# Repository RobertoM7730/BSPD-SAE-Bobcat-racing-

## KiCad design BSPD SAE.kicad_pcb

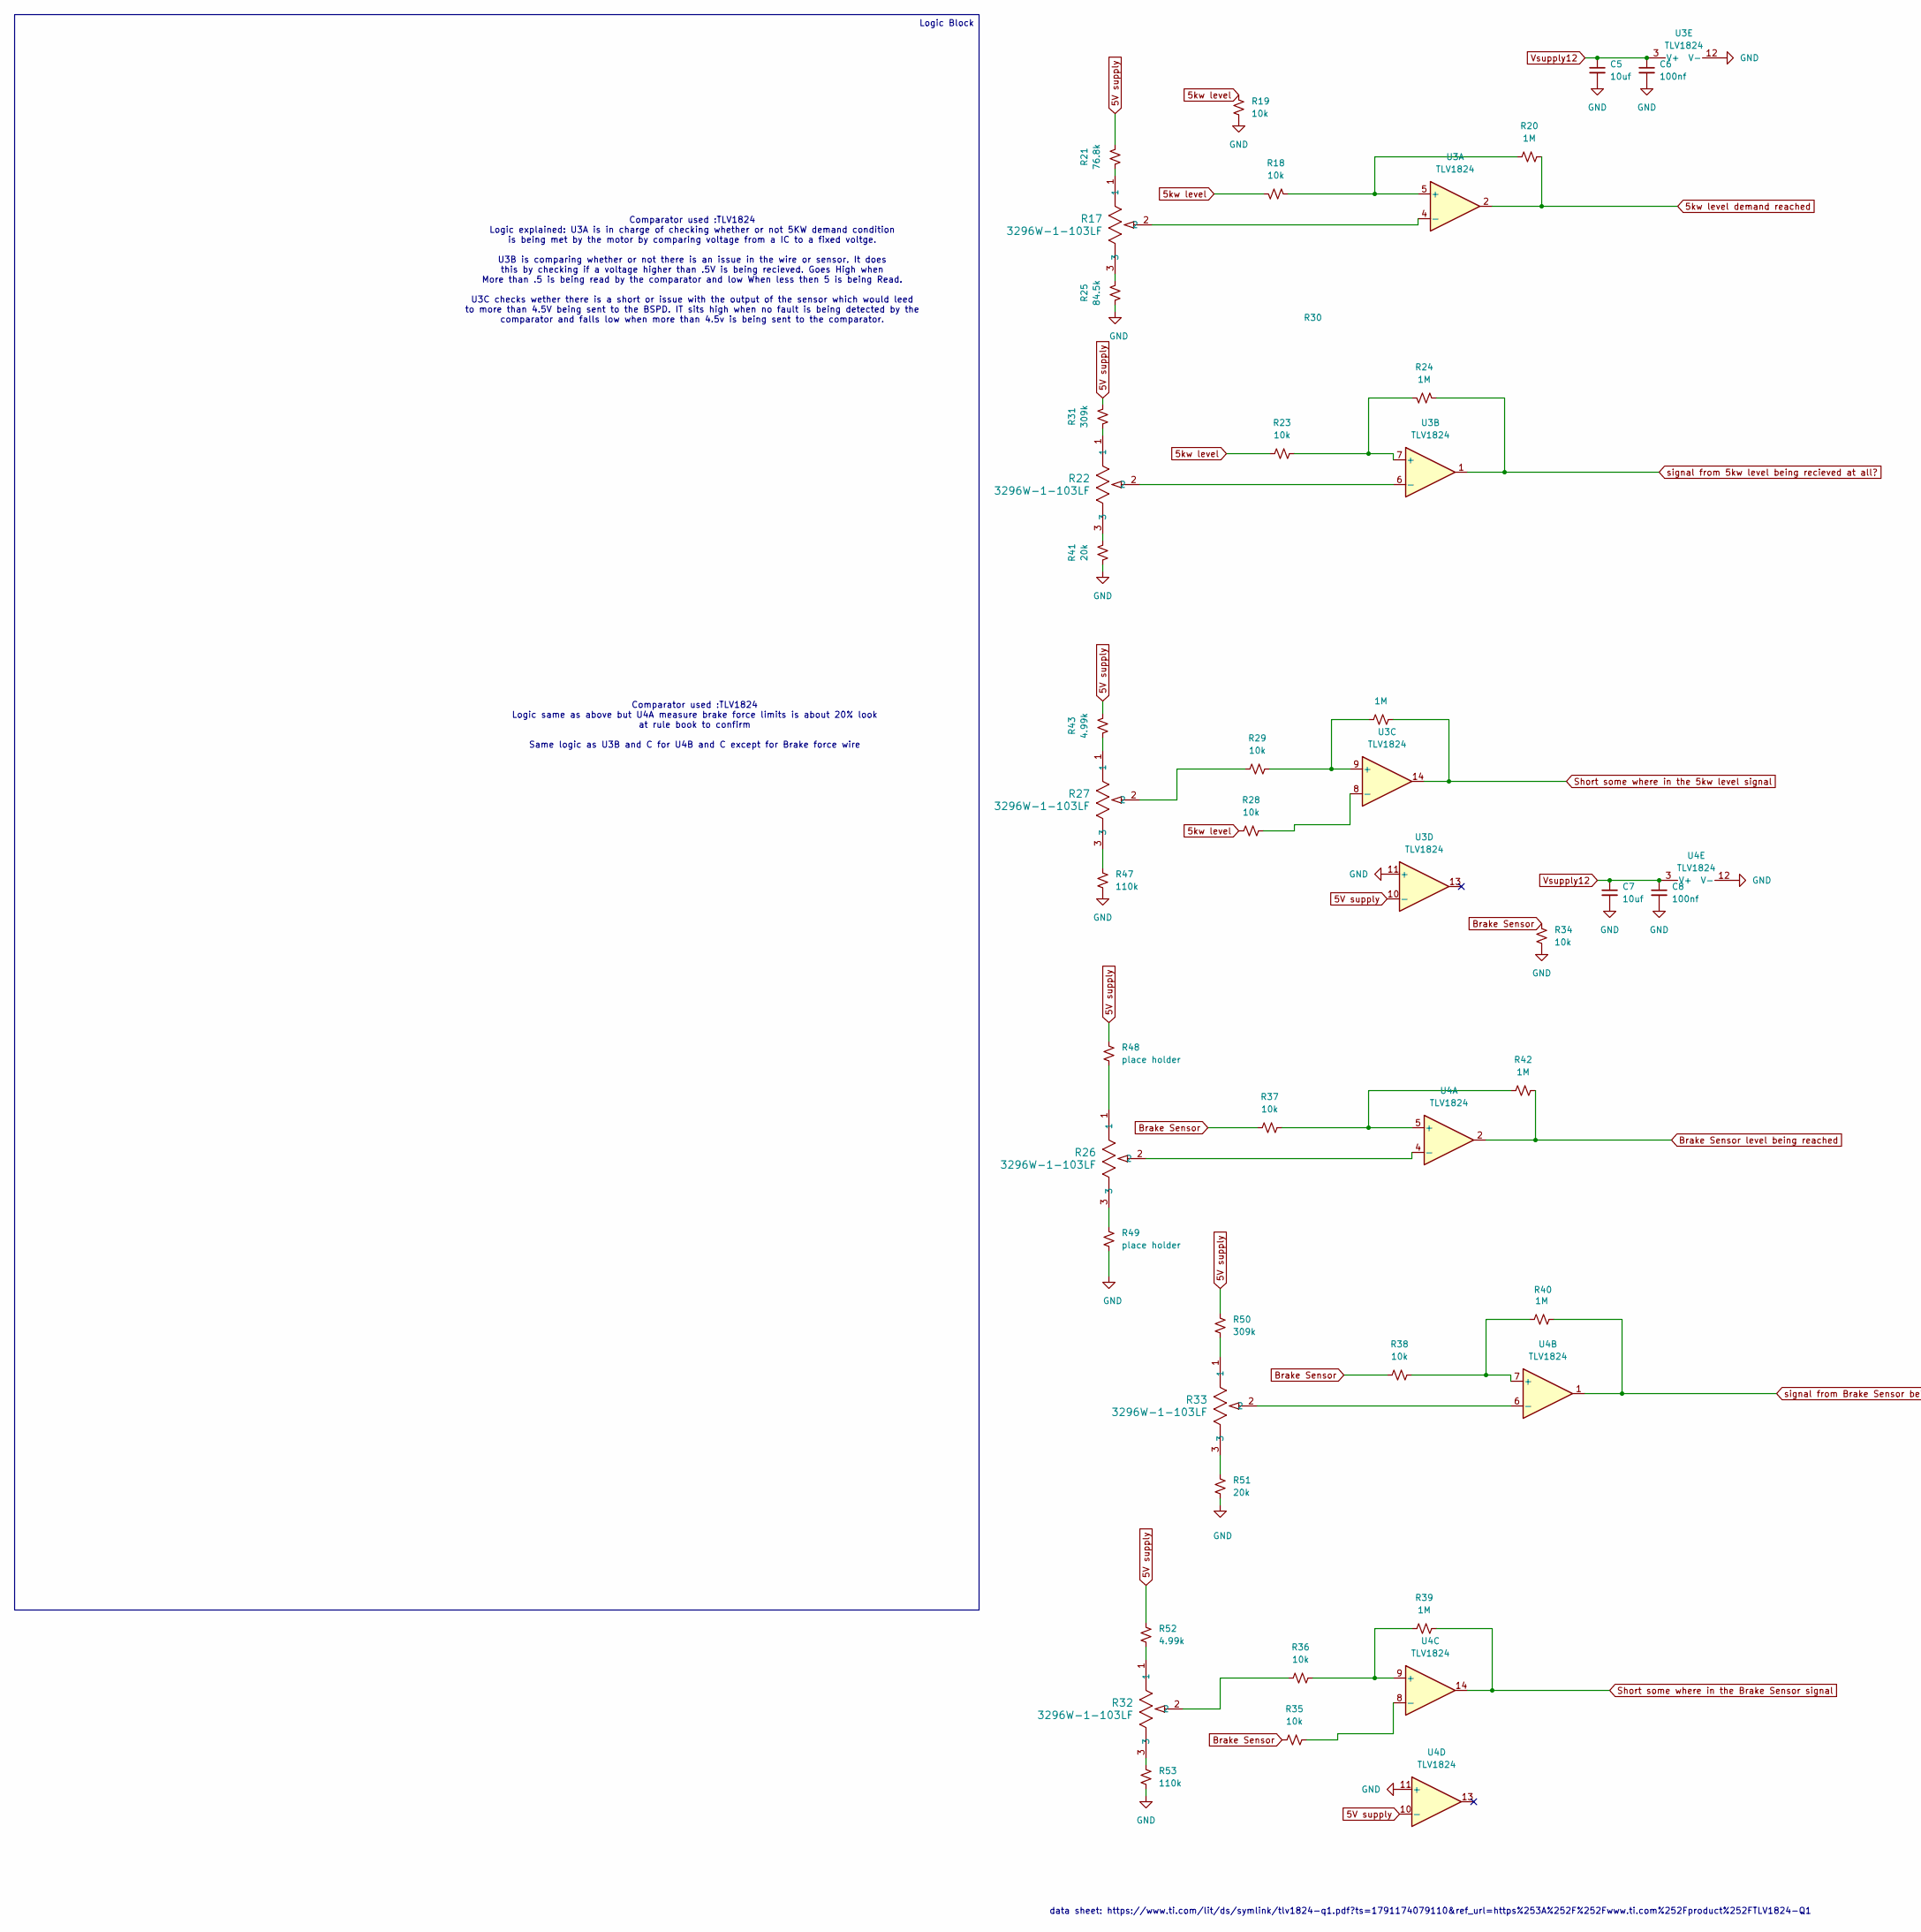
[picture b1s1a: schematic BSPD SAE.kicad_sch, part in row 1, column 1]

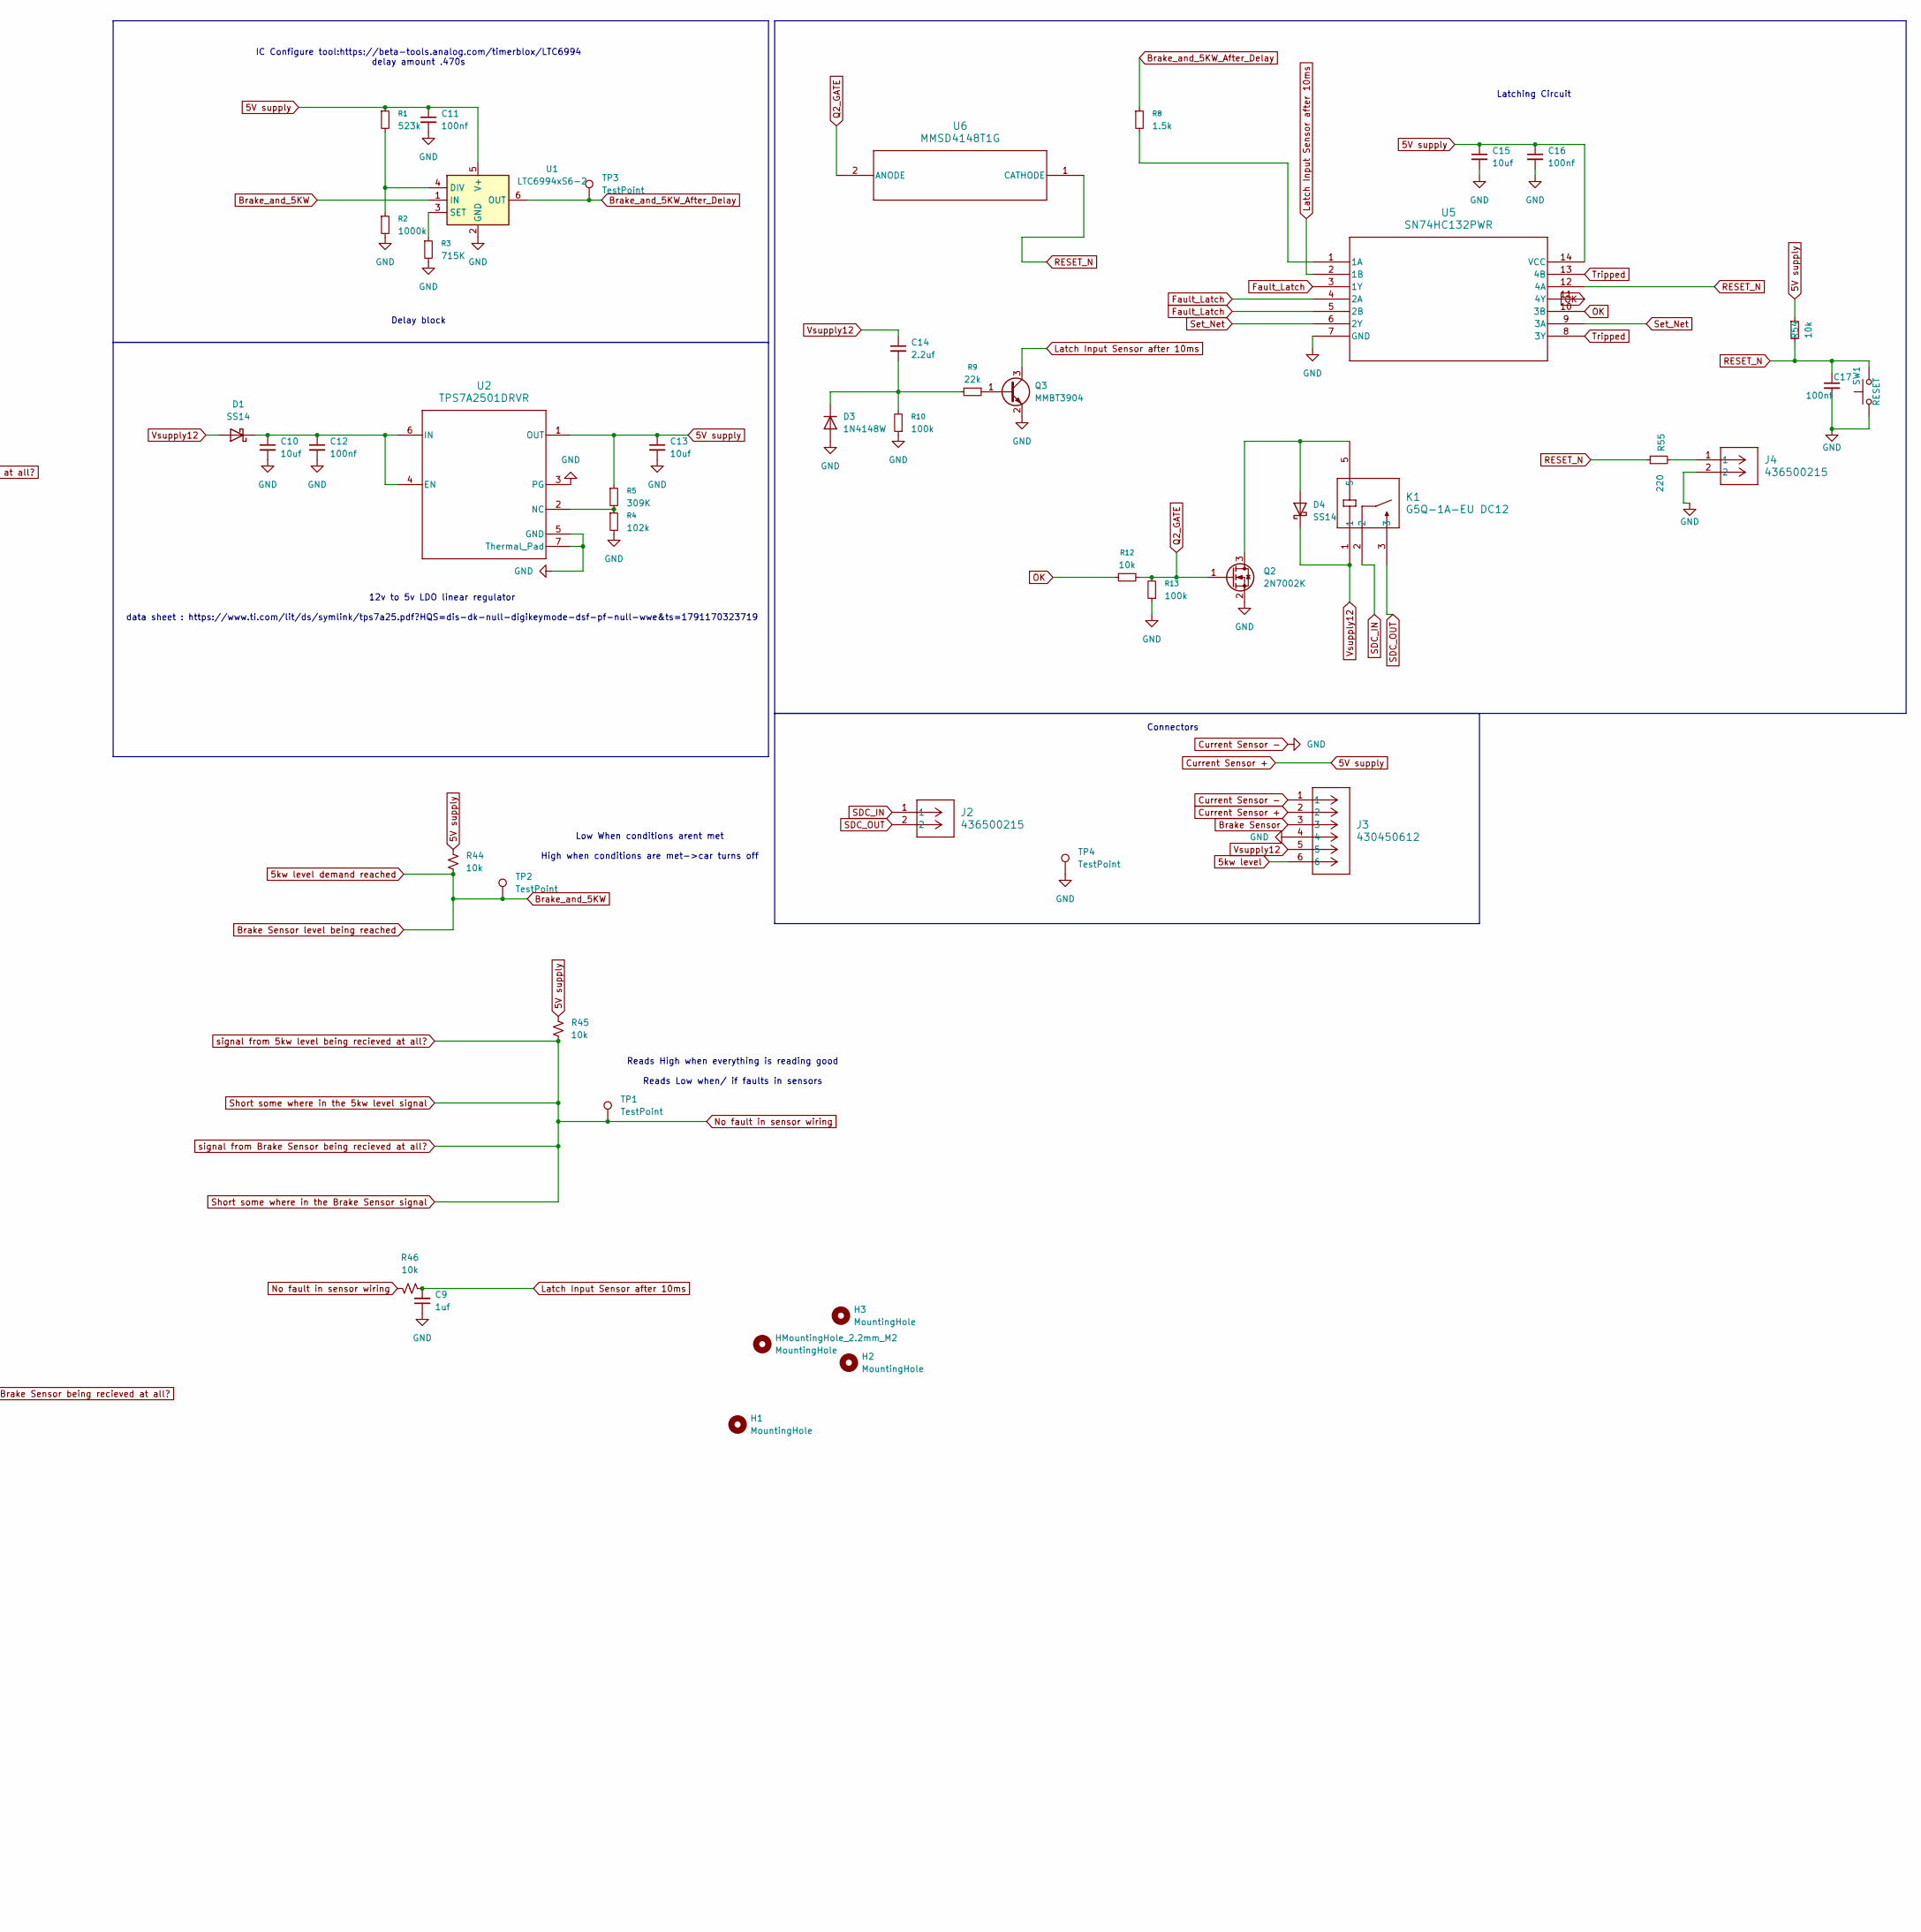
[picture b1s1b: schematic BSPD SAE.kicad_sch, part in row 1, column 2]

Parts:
C5, C7, C10, C13, C15: 10uf; C_0805_2012Metric
C6, C8, C11, C12, C16, C17: 100nf; C_0805_2012Metric
C9: 1uf; C_0805_2012Metric
C14: 2.2uf; C_0805_2012Metric
D1, D4: SS14; D_SMA
D3: 1N4148W; D_SOD-123
H1, H2, H3: MountingHole; MountingHole_2.2mm_M2
HMountingHole_2.2mm_M2: MountingHole; MountingHole_2.2mm_M2
J2, J4: 436500215; CONN_SD-43650-006_02_MOL
J3: 430450612; CONN_SD-43045-005_06_MOL
K1: G5Q-1A-EU DC12; RELAY_G5Q-1A DC5_OMR
Q2: 2N7002K; SOT-23
Q3: MMBT3904; SOT-23
R1: 523k; R_0805_2012Metric
R2: 1000k; R_0805_2012Metric
R3: 715K; R_0805_2012Metric
R4: 102k; R_0805_2012Metric
R5: 309K; R_0805_2012Metric
R8: 1.5k; R_0805_2012Metric
R9: 22k; R_0805_2012Metric
R10, R13: 100k; R_0805_2012Metric
R12, R18, R19, R23, R28, R29, R34, R35, R36, R37, R38, R44, R45, R46, R54: 10k; R_0805_2012Metric
R17, R22, R26, R27, R32, R33: 3296W-1-103LF; POT_3296W
R20, R24, R30, R39, R40, R42: 1M; R_0805_2012Metric
R21: 76.8k; R_0805_2012Metric
R25: 84.5k; R_0805_2012Metric
R31, R50: 309k; R_0805_2012Metric
R41, R51: 20k; R_0805_2012Metric
R43, R52: 4.99k; R_0805_2012Metric
R47, R53: 110k; R_0805_2012Metric
R48, R49: place holder; R_0805_2012Metric
R55: 220; R_0805_2012Metric
SW1: RESET; SW_SPST_Omron_B3FS-100xP; MPN PTS125SM43SMTR21M LFS; Digi-Key 108-PTS125SM43SMTR21MLFSCT-ND
TP1, TP2, TP3, TP4: TestPoint; TestPoint_THTPad_D1.0mm_Drill0.5mm
U1: LTC6994xS6-2; TSOT-23-6
U2: TPS7A2501DRVR; DRV0006A-IPC_A
U3, U4: TLV1824; TSSOP-14_4.4x5mm_P0.65mm_TI_PW
U5: SN74HC132PWR; PW14
U6: MMSD4148T1G; SOD-123_ONS

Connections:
5V supply: C11.1, C13.1, C15.1, C16.1, J3.2, R1.1, R5.1, R21.1, R31.1, R43.1, R44.2, R45.2, R48.2, R50.2, R52.2, R54.1, U1.5 (V+), U2.1 (OUT), U3.10 (-), U4.10 (-), U5.14 (VCC)
5kw level: J3.6, R18.2, R19.2, R23.1, R28.1
5kw level demand reached: R20.2, R42.2, R44.1, TP2.1 (1_1), U1.1 (IN), U3.2, U4.2
Brake Sensor: J3.3, R34.2, R35.1, R37.1, R38.1
Brake_and_5KW_After_Delay: R8.1, TP3.1 (1_1), U1.6 (OUT)
Current Sensor -: C5.2, C6.2, C7.2, C8.2, C9.1, C10.2, C11.2, C12.2, C13.2, C15.2, C16.2, C17.2, D3.2 (A), J3.1, J3.4, J4.2, Q2.2 (S), Q3.2 (E), R2.2, R3.2, R4.2, R10.1, R13.1, R19.1, R25.2, R34.1, R41.2, R47.1, R49.1, R51.1, R53.1, SW1.1, TP4.1 (1_1), U1.2 (GND), U2.3 (PG), U2.5 (GND), U2.7 (Thermal_Pad), U3.11 (+), U3.12 (V-), U4.11 (+), U4.12 (V-), U5.7 (GND)
Fault_Latch: U5.3 (1Y), U5.4 (2A), U5.5 (2B)
Latch Input Sensor after 10ms: C9.2, Q3.3 (C), R46.2, U5.2 (1B); also elsewhere on the board
unnamed: C10.1, C12.1, D1.1 (K), U2.4 (EN), U2.6 (IN)
unnamed: C14.2, D3.1 (K), R9.2, R10.2
unnamed: D4.2 (A), K1.5, Q2.3 (D)
unnamed: J4.1, R55.2
unnamed: Q3.1 (B), R9.1
unnamed: R17.1, R21.2
unnamed: R17.3, R25.1
unnamed: R22.1, R31.2
unnamed: R22.3, R41.1
unnamed: R26.1, R48.1
unnamed: R26.3, R49.2
unnamed: R27.1, R43.2
unnamed: R27.2, R29.1
unnamed: R27.3, R47.2
unnamed: R32.1, R52.1
unnamed: R32.2, R36.1
unnamed: R32.3, R53.2
unnamed: R33.1, R50.1
unnamed: R33.3, R51.2
unnamed: R1.2, R2.1, U1.4 (DIV)
unnamed: R3.1, U1.3 (SET)
unnamed: R4.1, R5.2, U2.2 (NC)
unnamed: R18.1, R20.1, U3.5 (+)
unnamed: R17.2, U3.4 (-)
unnamed: R23.2, R24.2, U3.7 (+)
unnamed: R22.2, U3.6 (-)
unnamed: R29.2, R30.1, U3.9 (+)
unnamed: R28.2, U3.8 (-)
unnamed: R37.2, R42.1, U4.5 (+)
unnamed: R26.2, U4.4 (-)
unnamed: R38.2, R40.1, U4.7 (+)
unnamed: R33.2, U4.6 (-)
unnamed: R36.2, R39.1, U4.9 (+)
unnamed: R35.2, U4.8 (-)
unnamed: R8.2, U5.1 (1A)
No fault in sensor wiring: R24.1, R30.2, R39.2, R40.2, R45.1, R46.1, TP1.1 (1_1), U3.1, U3.14, U4.1, U4.14
OK: R12.2, U5.10 (3B), U5.11 (4Y)
Q2_GATE: Q2.1 (G), R12.1, R13.2, U6.2 (ANODE)
RESET_N: C17.1, R54.2, R55.1, SW1.2, U5.12 (4A), U6.1 (CATHODE)
SDC_IN: J2.1, K1.2
SDC_OUT: J2.2, K1.3
Set_Net: U5.6 (2Y), U5.9 (3A)
Tripped: U5.8 (3Y), U5.13 (4B)
Vsupply12: C5.1, C6.1, C7.1, C8.1, C14.1, D1.2 (A), D4.1 (K), J3.5, K1.1, U3.3 (V+), U4.3 (V+)

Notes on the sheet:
Low When conditions arent met High when conditions are met->car turns off
12v to 5v LDO linear regulator data sheet : https://www.ti.com/lit/ds/symlink/tps7a25.pdf?HQS=dis-dk-null-digikeymode-dsf-pf-null-wwe&ts=1791170323719
IC Configure tool:https://beta-tools.analog.com/timerblox/LTC6994 delay amount .470s
data sheet: https://www.ti.com/lit/ds/symlink/tlv1824-q1.pdf?ts=1791174079110&ref_url=https%253A%252F%252Fwww.ti.com%252Fproduct%252FTLV1824-Q1
Comparator used :TLV1824 Logic same as above but U4A measure brake force limits is about 20% look at rule book to confirm Same logic as U3B and C for U4B and C except for Brake force wire
Comparator used :TLV1824 Logic explained: U3A is in charge of checking whether or not 5KW demand condition is being met by the motor by comparing voltage from a IC to a fixed voltge. U3B is comparing whether or not there is an issue in the wire or sensor. It does this by checking if a voltage highe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
Latching Circuit
Reads High when everything is reading good Reads Low when/ if faults in sensors
Delay block
Connectors
Logic Block

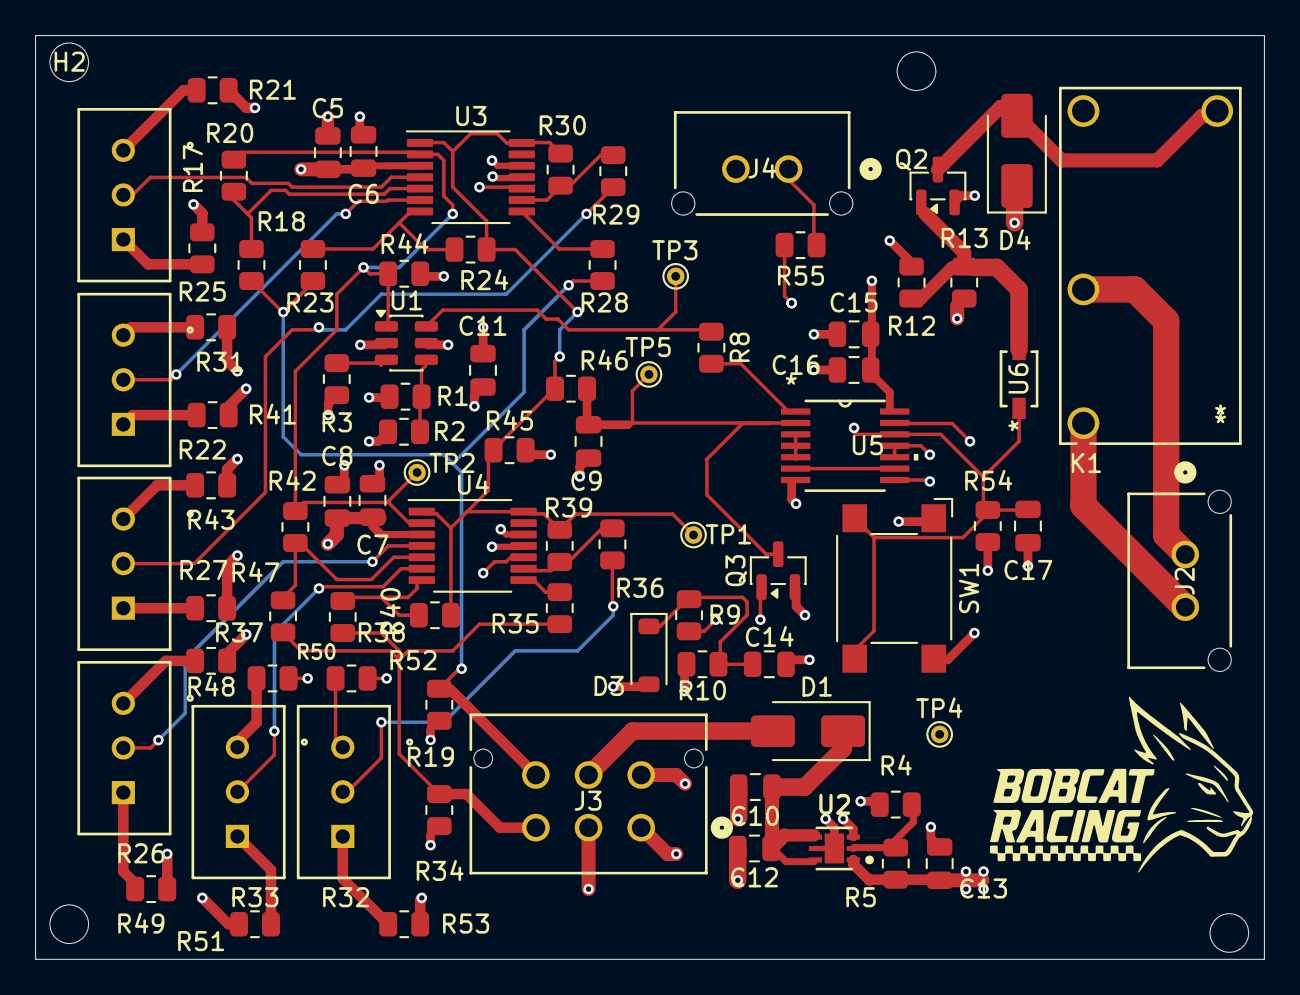
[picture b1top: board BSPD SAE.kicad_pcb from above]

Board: 4 copper layers, 70.0 x 52.6 mm, 87 parts (0 on the bottom side), 52 nets.

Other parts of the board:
TP5: TestPoint; TestPoint_THTPad_D1.0mm_Drill0.5mm

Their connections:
Latch Input Sensor after 10ms: TP5.1 (1_1); also elsewhere on the board

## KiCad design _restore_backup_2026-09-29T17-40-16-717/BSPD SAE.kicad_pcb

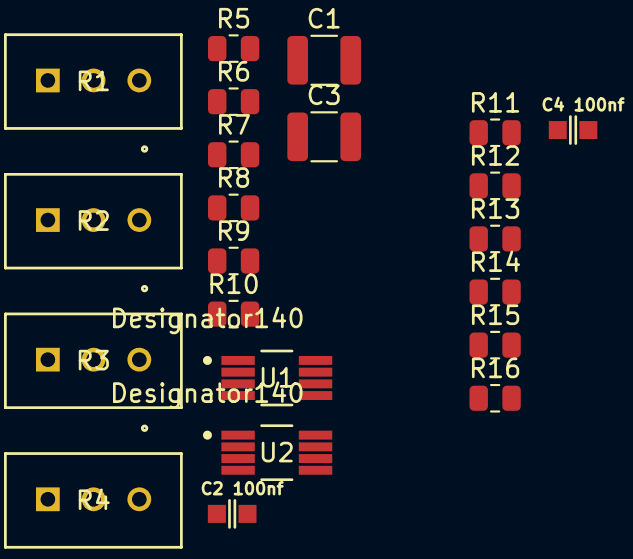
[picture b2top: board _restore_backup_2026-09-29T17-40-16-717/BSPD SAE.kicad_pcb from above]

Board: 2 copper layers, 22 parts (0 on the bottom side), 17 nets, no tracks yet.

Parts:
C1, C3: 10uf; C_1210_3225Metric
C2, C4: 100nf; C_0603
R1, R2, R3, R4: 3296W-1-103LF; POT_3296W
R5, R6, R9, R10, R11, R13, R14, R16: 10k; R_0805_2012Metric
R7, R8, R12, R15: 1M; R_0805_2012Metric
U1, U2: TLV1842QDGKRQ1; DGK0008A-IPC_A

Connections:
5V supply: R1.1, R2.1, R3.1, R4.1, R9.2, R10.2, R13.2, R16.2
GND: C1.2, C2.2, C3.2, C4.2, R1.3, R2.3, R3.3, R4.3, U1.4 (V-), U2.4 (V-)
Is Brake Pressed: R8.2, R9.1, U2.1 (OUT1)
Is Gas Pressed?: R7.2, R10.1, U1.1 (OUT1)
Is there voltage at Gas pedal Line: R15.2, R16.1, U1.7 (OUT2)
Is there voltage at brake pedal line: R12.2, R13.1, U2.7 (OUT2)
unnamed: R6.2, R7.1, U1.3 (IN1+)
unnamed: R1.2, U1.2 (IN1-)
unnamed: R14.2, R15.1, U1.5 (IN2+)
unnamed: R2.2, U1.6 (IN2-)
unnamed: R5.2, R8.1, U2.3 (IN1+)
unnamed: R3.2, U2.2 (IN1-)
unnamed: R11.2, R12.1, U2.5 (IN2+)
unnamed: R4.2, U2.6 (IN2-)
Vsig1: R6.1, R14.1
Vsig2: R5.1, R11.1
Vsupply12: C1.1, C2.1, C3.1, C4.1, U1.8 (V+), U2.8 (V+)
